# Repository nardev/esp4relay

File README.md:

Simple board with some SMD components.

- Hi-Link 100-240 VAC to 5 VDC
- HT7333A 3.3V voltage regulator
- 4x SONGLE  SRD-05VDC-SL-C
and other minor parts like resistors, capacitors etc...

Not tested but should work!

WORK IN PROGRESS

Order at: https://oshpark.com/projects/hfJpzOcm

<p>
&nbsp;&nbsp;
&nbsp;&nbsp;
&nbsp;&nbsp;
&nbsp;&nbsp;

</p>

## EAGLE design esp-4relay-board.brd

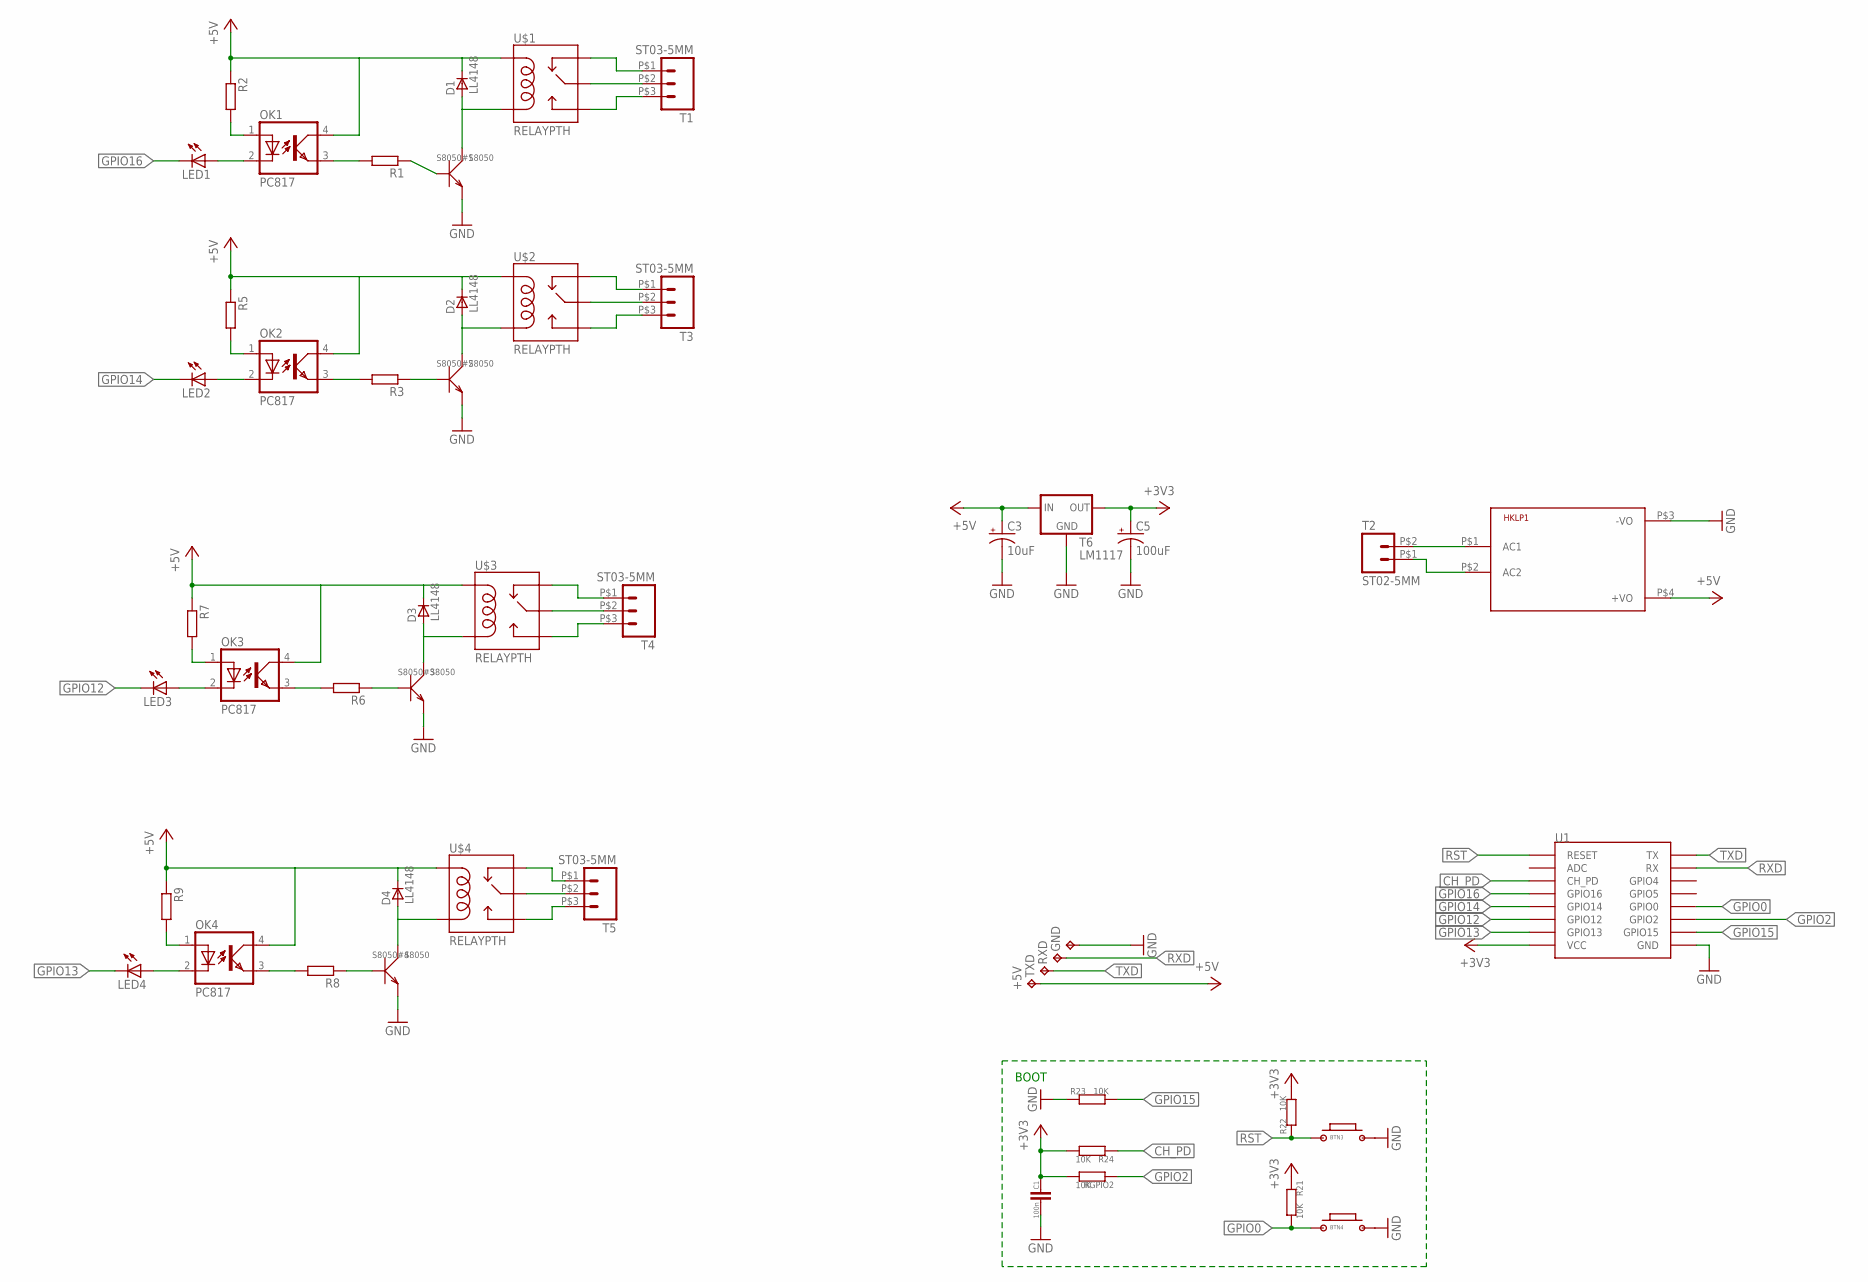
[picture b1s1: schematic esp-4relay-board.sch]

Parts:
+5V: TPTP15R; TP15R
BTN3, BTN4: BUTTON-2PSWITCH-TURTLE-2P; 2P-SWITCH-TURTLE
C1: 100n; C_0805
C3: 10uF; VISHAY_C
C5: 100uF; VISHAY_C
D1, D2, D3, D4: LL4148; SOD80_DO213AA_MINIMELF
GND: TPTP15R; TP15R
HKLP1: HKLPM01
LED1, LED2, LED3, LED4: LEDSML0805; SML0805
OK1, OK2, OK3, OK4: PC817; DIL04
R1, R2, R3, R5, R6, R7, R8, R9: R-EU_R1206; R1206
R21, R22, R23, R24: 10K; R_0805
RGPIO2: 10K; R_0805
RXD: TPTP15R; TP15R
S8050#1, S8050#2, S8050#3, S8050#4: S8050; SOT-23
T1, T3, T4, T5: ST03-5MM; EK500V-03P
T2: ST02-5MM; EK500V-02P
T6: LM1117; 78XXL
TXD: TPTP15R; TP15R
U1: ESP12
U$1, U$2, U$3, U$4: RELAYPTH; SRD-05VDC-SL-C

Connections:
+3V3: C1.1, C5.+, R21.1, R22.2, R24.2, RGPIO2.2, T6.GND (OUT), U1.VCC
+5V: +5V.TP, C3.+, D1.C, D2.C, D3.C, D4.C, HKLP1.P$4 (+VO), OK1.4 (COL), OK2.4 (COL), OK3.4 (COL), OK4.4 (COL), R2.1, R5.1, R7.1, R9.1, T6.OUT (IN), U$1.COIL1, U$2.COIL1, U$3.COIL1, U$4.COIL1
CH_PD: R24.1, U1.CH_PD
GND: BTN3.2, BTN4.2, C1.2, C3.-, C5.-, GND.TP, HKLP1.P$3 (-VO), R23.1, S8050#1.2 (E), S8050#2.2 (E), S8050#3.2 (E), S8050#4.2 (E), T6.IN (GND), U1.GND
GPIO0: BTN4.1, R21.2, U1.GPIO0
GPIO2: RGPIO2.1, U1.GPIO2
GPIO12: LED3.C, U1.GPIO12
GPIO13: LED4.C, U1.GPIO13
GPIO14: LED2.C, U1.GPIO14
GPIO15: R23.2, U1.GPIO15
GPIO16: LED1.C, U1.GPIO16
unnamed: OK1.3 (EMIT), R1.2
unnamed: R1.1, S8050#1.1 (B)
unnamed: T1.P$2 (2), U$1.SWCOMMON
unnamed: D1.A, S8050#1.3 (C), U$1.COIL0
unnamed: OK1.1 (A), R2.2
unnamed: LED1.A, OK1.2 (C)
unnamed: T1.P$3 (3), U$1.SWOPEN
unnamed: T1.P$1 (1), U$1.SWCLOSED (SWCLOSE)
unnamed: HKLP1.P$1 (AC1), T2.P$2 (2)
unnamed: HKLP1.P$2 (AC2), T2.P$1 (1)
unnamed: D2.A, S8050#2.3 (C), U$2.COIL0
unnamed: OK2.3 (EMIT), R3.2
unnamed: R3.1, S8050#2.1 (B)
unnamed: OK2.1 (A), R5.2
unnamed: LED2.A, OK2.2 (C)
unnamed: T3.P$2 (2), U$2.SWCOMMON
unnamed: T3.P$3 (3), U$2.SWOPEN
unnamed: T3.P$1 (1), U$2.SWCLOSED (SWCLOSE)
unnamed: D3.A, S8050#3.3 (C), U$3.COIL0
unnamed: OK3.3 (EMIT), R6.2
unnamed: R6.1, S8050#3.1 (B)
unnamed: OK3.1 (A), R7.2
unnamed: LED3.A, OK3.2 (C)
unnamed: T4.P$2 (2), U$3.SWCOMMON
unnamed: T4.P$3 (3), U$3.SWOPEN
unnamed: T4.P$1 (1), U$3.SWCLOSED (SWCLOSE)
unnamed: D4.A, S8050#4.3 (C), U$4.COIL0
unnamed: OK4.3 (EMIT), R8.2
unnamed: R8.1, S8050#4.1 (B)
unnamed: OK4.1 (A), R9.2
unnamed: LED4.A, OK4.2 (C)
unnamed: T5.P$2 (2), U$4.SWCOMMON
unnamed: T5.P$3 (3), U$4.SWOPEN
unnamed: T5.P$1 (1), U$4.SWCLOSED (SWCLOSE)
RST: BTN3.1, R22.1, U1.RESET
RXD: RXD.TP, U1.RX
TXD: TXD.TP, U1.TX

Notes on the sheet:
BOOT

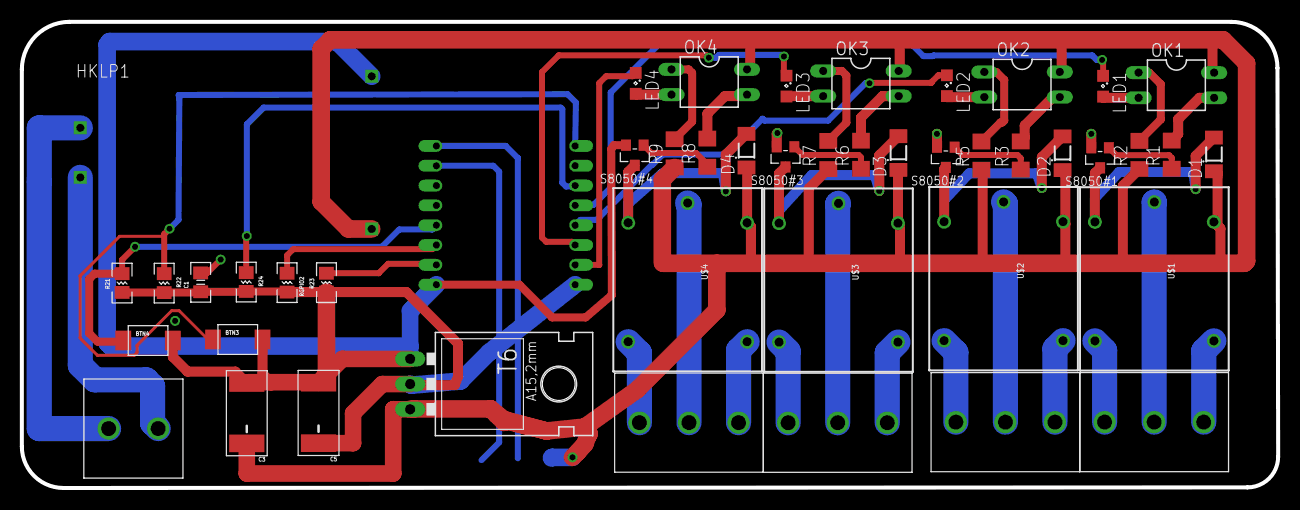
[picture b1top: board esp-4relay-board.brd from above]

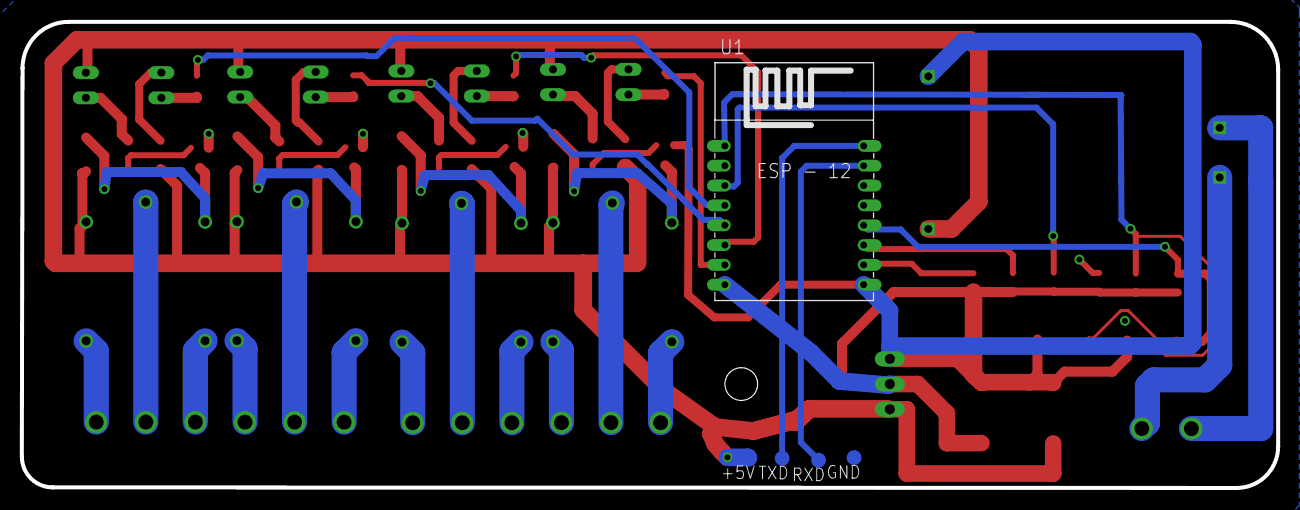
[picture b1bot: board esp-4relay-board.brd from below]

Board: 2 copper layers, 126.8 x 47.0 mm, 50 parts (5 on the bottom side), 48 nets.

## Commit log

2017-09-26 initial untested version
2017-09-26 README
2017-09-26 traces
2018-03-16 no optocops

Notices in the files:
parts and their libraries:
SparkFun-PowerIC: Licensing: Creative Commons ShareAlike 4.0 International - https://creativecommons.org/licenses/by-sa/4.0
